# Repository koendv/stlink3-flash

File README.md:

# stlink3-flash

This board adds 16 mbyte flash memory to [STLINK V3 MINI](https://www.st.com/zh/development-tools/stlink-v3mini.html), for storing micropython scripts.

[Schematic](docs/stlink3-flash-schematic.svg) 

BOM:

| Comp. | Desc          |
| ----- | ------------- |
| U1    | W25Q128JVSSIQ |
| C1    | 100n 0603     |
| R1    | 4k7 0603      |

Connections:

| Pin | Desc.     |
| --- | --------- |
| PE6 | SPI4_MOSI |
| PE5 | SPI4_MISO |
| PE4 | !FLASH_CS |
| PE2 | SPI4_SCK  |

Also solder ground and 3.3V.

[Gerber files](gerber.zip)

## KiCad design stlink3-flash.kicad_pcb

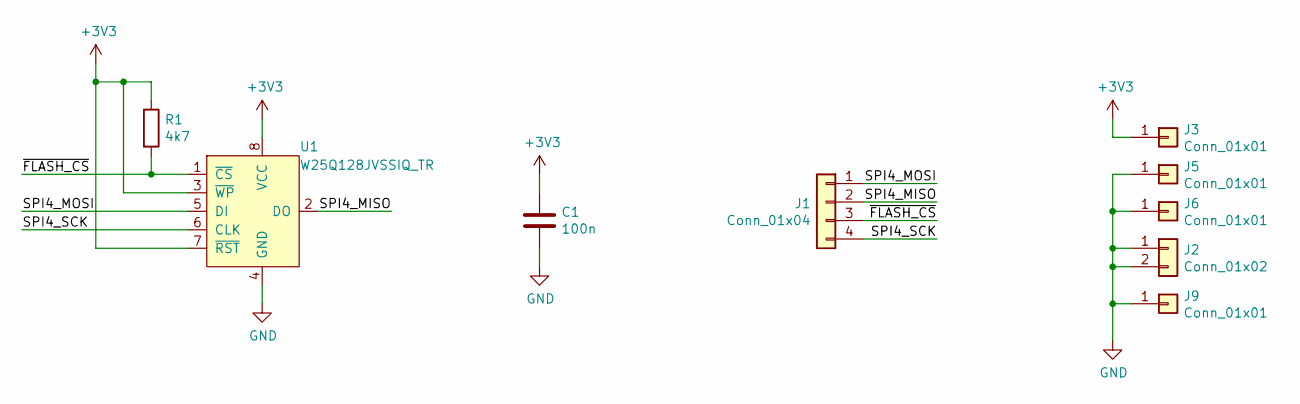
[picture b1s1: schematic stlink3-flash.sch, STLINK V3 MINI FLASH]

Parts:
C1: 100n; C_0603_1608Metric
J1: Conn_01x04; PinHeader_1x04_P1.27mm_Vertical
J2: Conn_01x02; PinHeader_1x02_P1.27mm_Vertical
J3, J5, J6, J9: Conn_01x01; PinHeader_1x01_P1.27mm_Vertical
R1: 4k7; R_0603_1608Metric
U1: W25Q128JVSSIQ_TR; SOIC-8_W5.6mm; MPN W25Q32JVSSIQ TR; Digi-Key_PN W25Q32JVSSIQCT-ND

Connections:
+3V3: C1.1, J3.1, R1.1, U1.3 (~WP), U1.7 (~RST), U1.8 (VCC)
/SPI4_MISO: J1.2, U1.2 (DO)
/SPI4_MOSI: J1.1, U1.5 (DI)
/SPI4_SCK: J1.4, U1.6 (CLK)
/~FLASH_CS~: J1.3, R1.2, U1.1 (~CS)
GND: C1.2, J2.1, J2.2, J5.1, J6.1, J9.1, U1.4 (GND)

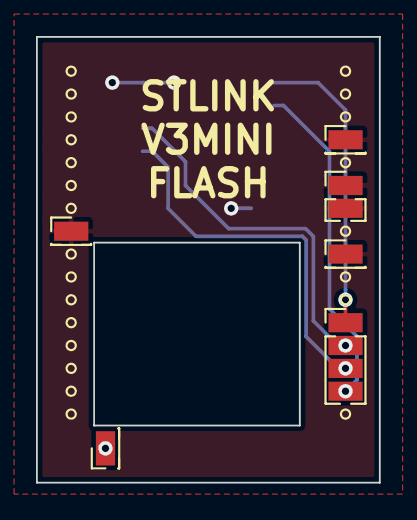
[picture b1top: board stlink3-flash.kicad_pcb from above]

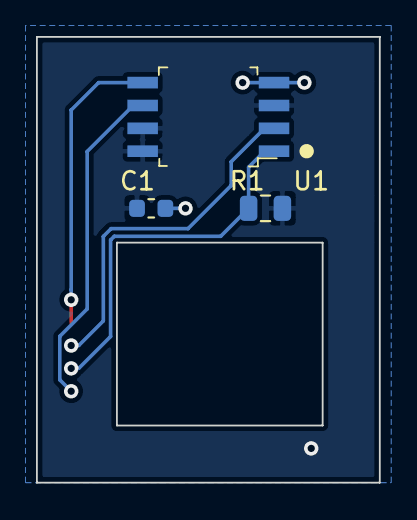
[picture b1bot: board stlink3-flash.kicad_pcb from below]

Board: 2 copper layers, 19.0 x 24.8 mm, 9 parts (3 on the bottom side), 6 nets.

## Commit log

2020-07-06 initial
2020-08-02 add gerber
2020-08-06 3d view
